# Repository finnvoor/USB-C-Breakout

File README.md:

# USB-C-Breakout
A breakout board for connecting USB-C to a breadboard, designed to be easily hand-solderable

### Components
- 1 * TYPE-C-31-M-12 Receptacle
- 1 * 2.54mm Pin Header (8-pin)
- 2 * 5.1k 1206 Chip Resistor (SMT)

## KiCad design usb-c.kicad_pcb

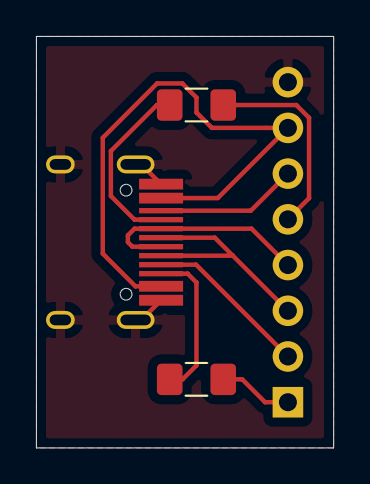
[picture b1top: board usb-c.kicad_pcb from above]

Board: 2 copper layers, 16.5 x 22.9 mm, 4 parts (1 on the bottom side), 10 nets.

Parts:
J1: Conn_01x08_Male; PinHeader_1x08_P2.54mm_Vertical
R1, R2: 5.1k; R_1206_3216Metric_Pad1.42x1.75mm_HandSolder
USB1: HRO-TYPE-C-31-M-12; HRO-TYPE-C-31-M-12-HandSoldering

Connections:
CC1: J1.5, R1.1
CC2: J1.1, R2.1
D+: J1.3, USB1.6, USB1.8
D-: J1.4, USB1.5, USB1.7
Earth: J1.8, USB1.1, USB1.12, USB1.13
unnamed: R1.2, USB1.4
unnamed: R2.2, USB1.10
SBU1: J1.2, USB1.9
SBU2: J1.6, USB1.3
VBUS: J1.7, USB1.2, USB1.11

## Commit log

2020-01-06 File Structure
2020-01-06 Add img
2020-01-06 Add pinout silkscreen
2020-01-06 Update pinout
